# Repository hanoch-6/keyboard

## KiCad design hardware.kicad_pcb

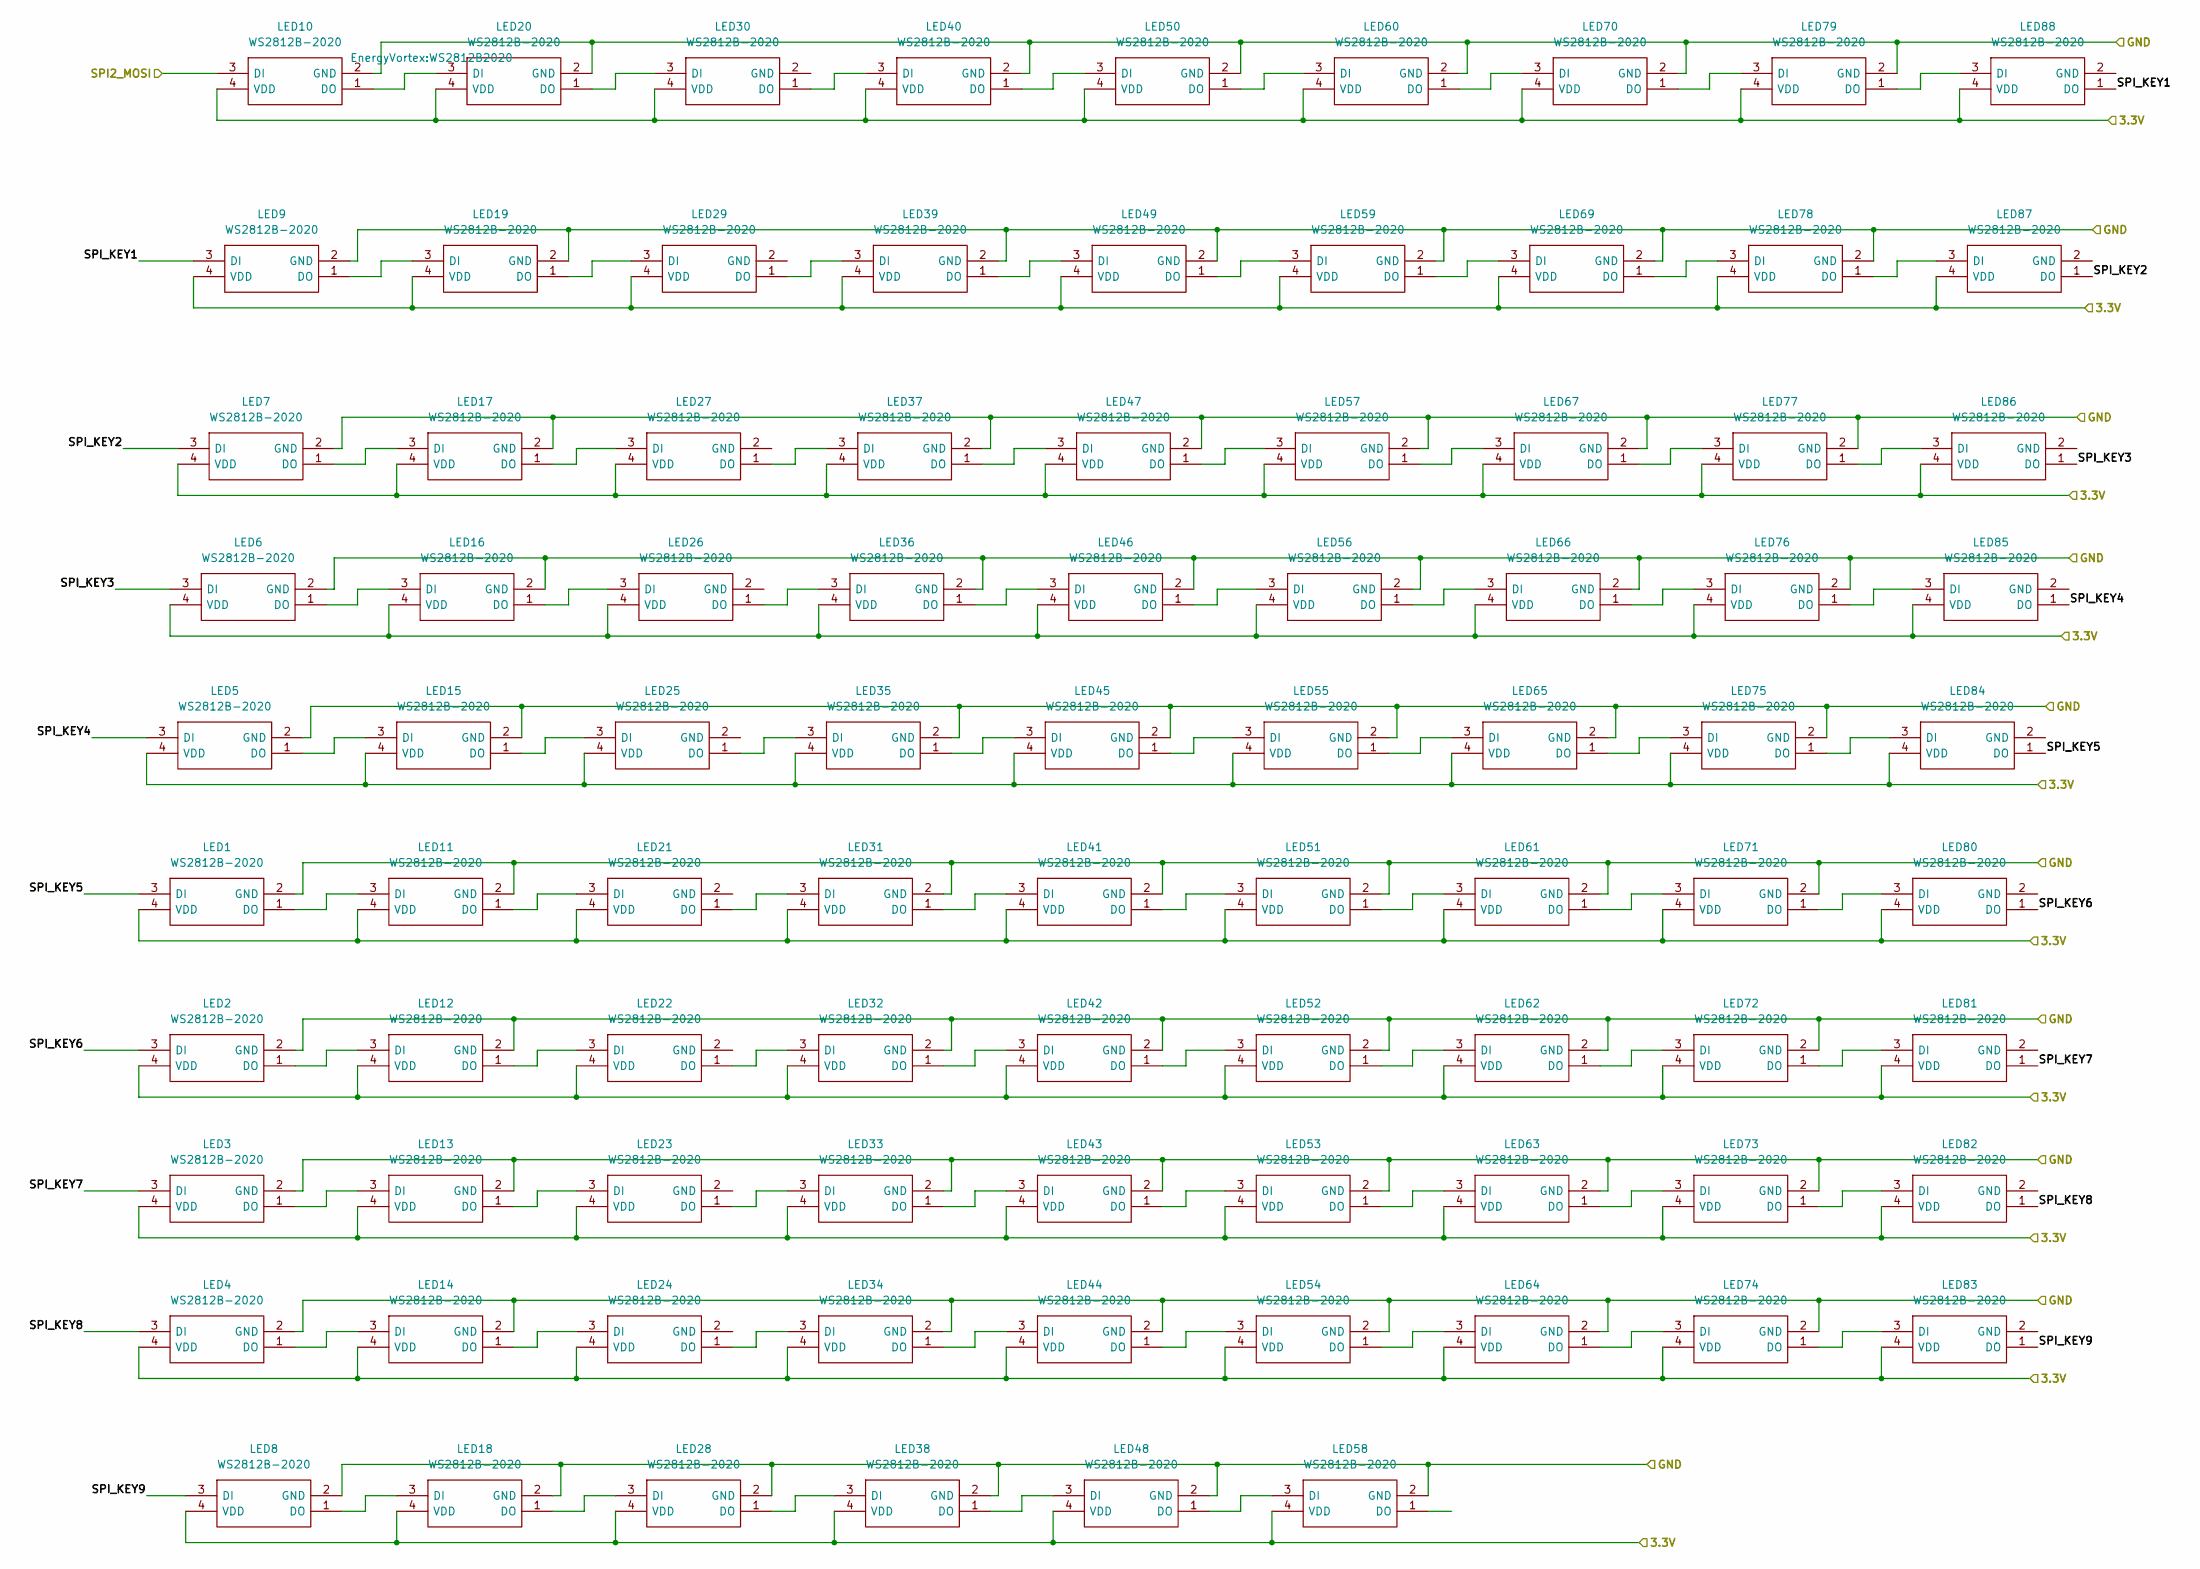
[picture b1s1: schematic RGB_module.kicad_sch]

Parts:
LED1, LED2, LED3, LED4, LED5, LED6, LED7, LED8, LED9, LED10, LED11, LED12, LED13, LED14, LED15, LED16, LED17, LED18, LED19, LED20, LED21, LED22, LED23, LED24, LED25, LED26, LED27, LED28, LED29, LED30, LED31, LED32, LED33, LED34, LED35, LED36, LED37, LED38, LED39, LED40, LED41, LED42, LED43, LED44, LED45, LED46, LED47, LED48, LED49, LED50, LED51, LED52, LED53, LED54, LED55, LED56, LED57, LED58, LED59, LED60, LED61, LED62, LED63, LED64, LED65, LED66, LED67, LED69, LED70, LED71, LED72, LED73, LED74, LED75, LED76, LED77, LED78, LED79, LED80, LED81, LED82, LED83, LED84, LED85, LED86, LED87, LED88: WS2812B-2020; WS2812B2020; Manufacturer_Part_Number WS2812B-2020

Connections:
+3.3V: LED1.4 (VDD), LED2.4 (VDD), LED3.4 (VDD), LED4.4 (VDD), LED5.4 (VDD), LED6.4 (VDD), LED7.4 (VDD), LED8.4 (VDD), LED9.4 (VDD), LED10.4 (VDD), LED11.4 (VDD), LED12.4 (VDD), LED13.4 (VDD), LED14.4 (VDD), LED15.4 (VDD), LED16.4 (VDD), LED17.4 (VDD), LED18.4 (VDD), LED19.4 (VDD), LED20.4 (VDD), LED21.4 (VDD), LED22.4 (VDD), LED23.4 (VDD), LED24.4 (VDD), LED25.4 (VDD), LED26.4 (VDD), LED27.4 (VDD), LED28.4 (VDD), LED29.4 (VDD), LED30.4 (VDD), LED31.4 (VDD), LED32.4 (VDD), LED33.4 (VDD), LED34.4 (VDD), LED35.4 (VDD), LED36.4 (VDD), LED37.4 (VDD), LED38.4 (VDD), LED39.4 (VDD), LED40.4 (VDD), LED41.4 (VDD), LED42.4 (VDD), LED43.4 (VDD), LED44.4 (VDD), LED45.4 (VDD), LED46.4 (VDD), LED47.4 (VDD), LED48.4 (VDD), LED49.4 (VDD), LED50.4 (VDD), LED51.4 (VDD), LED52.4 (VDD), LED53.4 (VDD), LED54.4 (VDD), LED55.4 (VDD), LED56.4 (VDD), LED57.4 (VDD), LED58.4 (VDD), LED59.4 (VDD), LED60.4 (VDD), LED61.4 (VDD), LED62.4 (VDD), LED63.4 (VDD), LED64.4 (VDD), LED65.4 (VDD), LED66.4 (VDD), LED67.4 (VDD), LED69.4 (VDD), LED70.4 (VDD), LED71.4 (VDD), LED72.4 (VDD), LED73.4 (VDD), LED74.4 (VDD), LED75.4 (VDD), LED76.4 (VDD), LED77.4 (VDD), LED78.4 (VDD), LED79.4 (VDD), LED80.4 (VDD), LED81.4 (VDD), LED82.4 (VDD), LED83.4 (VDD), LED84.4 (VDD), LED85.4 (VDD), LED86.4 (VDD), LED87.4 (VDD), LED88.4 (VDD); also elsewhere on the board
/MCU/SPI2_MOSI: LED10.3 (DI); also elsewhere on the board
/RGB_module/SPI_KEY1: LED9.3 (DI), LED88.1 (DO)
/RGB_module/SPI_KEY2: LED7.3 (DI), LED87.1 (DO)
/RGB_module/SPI_KEY3: LED6.3 (DI), LED86.1 (DO)
/RGB_module/SPI_KEY4: LED5.3 (DI), LED85.1 (DO)
/RGB_module/SPI_KEY5: LED1.3 (DI), LED84.1 (DO)
/RGB_module/SPI_KEY6: LED2.3 (DI), LED80.1 (DO)
/RGB_module/SPI_KEY7: LED3.3 (DI), LED81.1 (DO)
/RGB_module/SPI_KEY8: LED4.3 (DI), LED82.1 (DO)
/RGB_module/SPI_KEY9: LED8.3 (DI), LED83.1 (DO)
GND: LED1.2 (GND), LED2.2 (GND), LED3.2 (GND), LED4.2 (GND), LED5.2 (GND), LED6.2 (GND), LED7.2 (GND), LED8.2 (GND), LED9.2 (GND), LED10.2 (GND), LED11.2 (GND), LED12.2 (GND), LED13.2 (GND), LED14.2 (GND), LED15.2 (GND), LED16.2 (GND), LED17.2 (GND), LED18.2 (GND), LED19.2 (GND), LED20.2 (GND), LED28.2 (GND), LED31.2 (GND), LED32.2 (GND), LED33.2 (GND), LED34.2 (GND), LED35.2 (GND), LED36.2 (GND), LED37.2 (GND), LED38.2 (GND), LED39.2 (GND), LED40.2 (GND), LED41.2 (GND), LED42.2 (GND), LED43.2 (GND), LED44.2 (GND), LED45.2 (GND), LED46.2 (GND), LED47.2 (GND), LED48.2 (GND), LED49.2 (GND), LED50.2 (GND), LED51.2 (GND), LED52.2 (GND), LED53.2 (GND), LED54.2 (GND), LED55.2 (GND), LED56.2 (GND), LED57.2 (GND), LED58.2 (GND), LED59.2 (GND), LED60.2 (GND), LED61.2 (GND), LED62.2 (GND), LED63.2 (GND), LED64.2 (GND), LED65.2 (GND), LED66.2 (GND), LED67.2 (GND), LED69.2 (GND), LED70.2 (GND), LED71.2 (GND), LED72.2 (GND), LED73.2 (GND), LED74.2 (GND), LED75.2 (GND), LED76.2 (GND), LED77.2 (GND), LED78.2 (GND), LED79.2 (GND); also elsewhere on the board
unnamed: LED1.1 (DO), LED11.3 (DI)
unnamed: LED10.1 (DO), LED20.3 (DI)
unnamed: LED11.1 (DO), LED21.3 (DI)
unnamed: LED12.1 (DO), LED22.3 (DI)
unnamed: LED2.1 (DO), LED12.3 (DI)
unnamed: LED13.1 (DO), LED23.3 (DI)
unnamed: LED3.1 (DO), LED13.3 (DI)
unnamed: LED14.1 (DO), LED24.3 (DI)
unnamed: LED4.1 (DO), LED14.3 (DI)
unnamed: LED15.1 (DO), LED25.3 (DI)
unnamed: LED5.1 (DO), LED15.3 (DI)
unnamed: LED16.1 (DO), LED26.3 (DI)
unnamed: LED6.1 (DO), LED16.3 (DI)
unnamed: LED17.1 (DO), LED27.3 (DI)
unnamed: LED7.1 (DO), LED17.3 (DI)
unnamed: LED18.1 (DO), LED28.3 (DI)
unnamed: LED8.1 (DO), LED18.3 (DI)
unnamed: LED19.1 (DO), LED29.3 (DI)
unnamed: LED9.1 (DO), LED19.3 (DI)
unnamed: LED20.1 (DO), LED30.3 (DI)
unnamed: LED21.1 (DO), LED31.3 (DI)
unnamed: LED22.1 (DO), LED32.3 (DI)
unnamed: LED23.1 (DO), LED33.3 (DI)
unnamed: LED24.1 (DO), LED34.3 (DI)
unnamed: LED25.1 (DO), LED35.3 (DI)
unnamed: LED26.1 (DO), LED36.3 (DI)
unnamed: LED27.1 (DO), LED37.3 (DI)
unnamed: LED28.1 (DO), LED38.3 (DI)
unnamed: LED29.1 (DO), LED39.3 (DI)
unnamed: LED30.1 (DO), LED40.3 (DI)
unnamed: LED31.1 (DO), LED41.3 (DI)
unnamed: LED32.1 (DO), LED42.3 (DI)
unnamed: LED33.1 (DO), LED43.3 (DI)
unnamed: LED34.1 (DO), LED44.3 (DI)
unnamed: LED35.1 (DO), LED45.3 (DI)
unnamed: LED36.1 (DO), LED46.3 (DI)
unnamed: LED37.1 (DO), LED47.3 (DI)
unnamed: LED38.1 (DO), LED48.3 (DI)
unnamed: LED39.1 (DO), LED49.3 (DI)
unnamed: LED40.1 (DO), LED50.3 (DI)
unnamed: LED41.1 (DO), LED51.3 (DI)
unnamed: LED42.1 (DO), LED52.3 (DI)
unnamed: LED43.1 (DO), LED53.3 (DI)
unnamed: LED44.1 (DO), LED54.3 (DI)
unnamed: LED45.1 (DO), LED55.3 (DI)
unnamed: LED46.1 (DO), LED56.3 (DI)
unnamed: LED47.1 (DO), LED57.3 (DI)
unnamed: LED48.1 (DO), LED58.3 (DI)
unnamed: LED49.1 (DO), LED59.3 (DI)
unnamed: LED50.1 (DO), LED60.3 (DI)
unnamed: LED51.1 (DO), LED61.3 (DI)
unnamed: LED52.1 (DO), LED62.3 (DI)
unnamed: LED53.1 (DO), LED63.3 (DI)
unnamed: LED54.1 (DO), LED64.3 (DI)
unnamed: LED55.1 (DO), LED65.3 (DI)
unnamed: LED56.1 (DO), LED66.3 (DI)
unnamed: LED57.1 (DO), LED67.3 (DI)
unnamed: LED59.1 (DO), LED69.3 (DI)
unnamed: LED60.1 (DO), LED70.3 (DI)
unnamed: LED61.1 (DO), LED71.3 (DI)
unnamed: LED62.1 (DO), LED72.3 (DI)
unnamed: LED63.1 (DO), LED73.3 (DI)
unnamed: LED64.1 (DO), LED74.3 (DI)
unnamed: LED65.1 (DO), LED75.3 (DI)
unnamed: LED66.1 (DO), LED76.3 (DI)
unnamed: LED67.1 (DO), LED77.3 (DI)
unnamed: LED69.1 (DO), LED78.3 (DI)
unnamed: LED70.1 (DO), LED79.3 (DI)
unnamed: LED71.1 (DO), LED80.3 (DI)
unnamed: LED72.1 (DO), LED81.3 (DI)
unnamed: LED73.1 (DO), LED82.3 (DI)
unnamed: LED74.1 (DO), LED83.3 (DI)
unnamed: LED75.1 (DO), LED84.3 (DI)
unnamed: LED76.1 (DO), LED85.3 (DI)
unnamed: LED77.1 (DO), LED86.3 (DI)
unnamed: LED78.1 (DO), LED87.3 (DI)
unnamed: LED79.1 (DO), LED88.3 (DI)

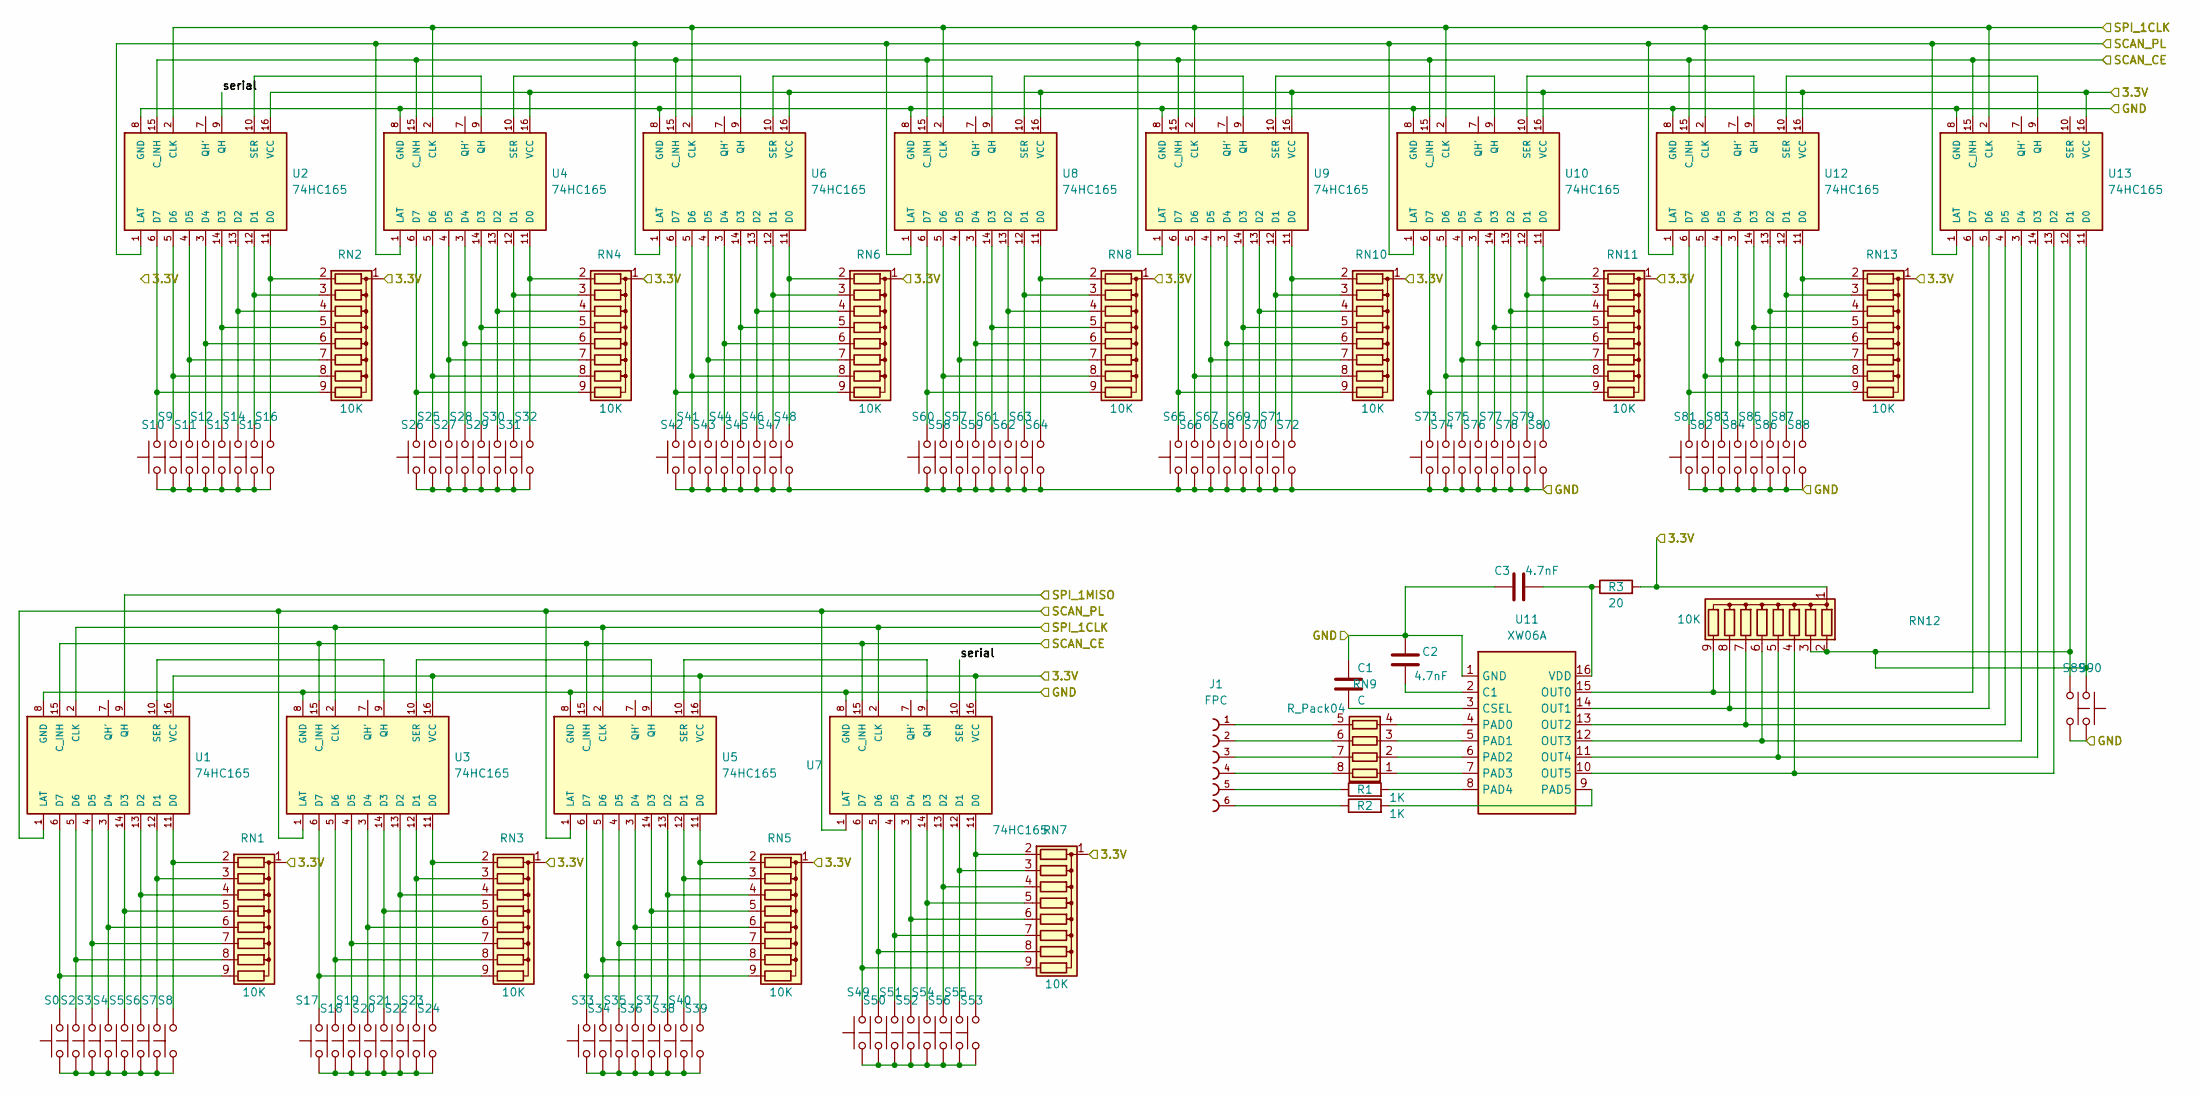
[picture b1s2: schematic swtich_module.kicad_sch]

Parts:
C1: C; C_0603_1608Metric
C2, C3: 4.7nF; C_0603_1608Metric
J1: FPC; FPC-0.5mm-6PIN
R1, R2: 1K; R_0603_1608Metric
R3: 20; R_0603_1608Metric
RN1, RN2, RN3, RN4, RN5, RN6, RN7, RN8, RN10, RN11, RN12, RN13: 10K; R_Array_Convex_8x0602
RN9: R_Pack04; R_Array_Convex_4x0603
S0, S2, S3, S4, S5, S6, S7, S8, S9, S10, S11, S12, S13, S14, S15, S16, S17, S18, S19, S20, S21, S22, S23, S24, S25, S26, S27, S28, S29, S30, S31, S32, S33, S34, S35, S36, S37, S38, S39, S40, S41, S42, S43, S44, S45, S46, S47, S48, S49, S50, S51, S52, S53, S54, S55, S56, S57, S58, S59, S60, S61, S62, S63, S64, S65, S66, S67, S68, S69, S70, S71, S72, S73, S74, S75, S76, S77, S78, S79, S80, S81, S82, S83, S84, S85, S86, S87, S88, S89, S90: SW_Push; CHERRY-MX-LED
U1, U2, U3, U4, U5, U6, U7, U8, U9, U10, U12, U13: 74HC165; SO-16
U11: XW06A; SOIC-16_3.9x9.9mm_P1.27mm

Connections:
+3.3V: R3.2, RN1.1 (common), RN2.1 (common), RN3.1 (common), RN4.1 (common), RN5.1 (common), RN6.1 (common), RN7.1 (common), RN8.1 (common), RN10.1 (common), RN11.1 (common), RN12.1 (common), RN13.1 (common), U1.16 (VCC), U2.16 (VCC), U3.16 (VCC), U4.16 (VCC), U5.16 (VCC), U6.16 (VCC), U7.16 (VCC), U8.16 (VCC), U9.16 (VCC), U10.16 (VCC), U12.16 (VCC), U13.16 (VCC); also elsewhere on the board
/MCU/SCAN_CE: U1.15 (C_INH), U2.15 (C_INH), U3.15 (C_INH), U4.15 (C_INH), U5.15 (C_INH), U6.15 (C_INH), U7.15 (C_INH), U8.15 (C_INH), U9.15 (C_INH), U10.15 (C_INH), U12.15 (C_INH), U13.15 (C_INH); also elsewhere on the board
/MCU/SCAN_PL: U1.1 (LAT), U2.1 (LAT), U3.1 (LAT), U4.1 (LAT), U5.1 (LAT), U6.1 (LAT), U7.1 (LAT), U8.1 (LAT), U9.1 (LAT), U10.1 (LAT), U12.1 (LAT), U13.1 (LAT); also elsewhere on the board
/MCU/SPI1_CLK: U1.2 (CLK), U2.2 (CLK), U3.2 (CLK), U4.2 (CLK), U5.2 (CLK), U6.2 (CLK), U7.2 (CLK), U8.2 (CLK), U9.2 (CLK), U10.2 (CLK), U12.2 (CLK), U13.2 (CLK); also elsewhere on the board
/MCU/SPI1_MISO: U1.9 (QH); also elsewhere on the board
/swtich_module/serial: U2.9 (QH), U7.10 (SER)
GND: C1.2, C2.2, C3.2, S41.1, S42.1, S43.1, S44.1, S45.1, S46.1, S47.1, S48.1, S57.1, S58.1, S59.1, S60.1, S61.1, S62.1, S63.1, S64.1, S65.1, S66.1, S67.1, S68.1, S69.1, S70.1, S71.1, S72.1, S73.1, S74.1, S75.1, S76.1, S77.1, S78.1, S79.1, S80.1, S81.1, S82.1, S83.1, S84.1, S85.1, S86.1, S87.1, S88.1, S89.1, S90.1, U1.8 (GND), U2.8 (GND), U3.8 (GND), U4.8 (GND), U5.8 (GND), U6.8 (GND), U7.8 (GND), U8.8 (GND), U9.8 (GND), U10.8 (GND), U11.1 (GND), U12.8 (GND), U13.8 (GND); also elsewhere on the board
unnamed: C1.1, U11.3 (CSEL)
unnamed: C2.1, U11.2 (C1)
unnamed: C3.1, R3.1, U11.16 (VDD)
unnamed: J1.1, RN9.5 (R4.2)
unnamed: J1.2, RN9.6 (R3.2)
unnamed: J1.3, RN9.7 (R2.2)
unnamed: J1.4, RN9.8 (R1.2)
unnamed: J1.5, R1.1
unnamed: J1.6, R2.1
unnamed: R1.2, U11.8 (PAD4)
unnamed: R2.2, U11.9 (PAD5)
unnamed: RN1.2 (R1), S8.2, U1.11 (D0)
unnamed: RN1.3 (R2), S7.2, U1.12 (D1)
unnamed: RN1.4 (R3), S6.2, U1.13 (D2)
unnamed: RN1.5 (R4), S5.2, U1.14 (D3)
unnamed: RN1.6 (R5), S4.2, U1.3 (D4)
unnamed: RN1.7 (R6), S3.2, U1.4 (D5)
unnamed: RN1.8 (R7), S2.2, U1.5 (D6)
unnamed: RN1.9 (R8), S0.2, U1.6 (D7)
unnamed: RN2.2 (R1), S16.2, U2.11 (D0)
unnamed: RN2.3 (R2), S15.2, U2.12 (D1)
unnamed: RN2.4 (R3), S14.2, U2.13 (D2)
unnamed: RN2.5 (R4), S13.2, U2.14 (D3)
unnamed: RN2.6 (R5), S12.2, U2.3 (D4)
unnamed: RN2.7 (R6), S11.2, U2.4 (D5)
unnamed: RN2.8 (R7), S9.2, U2.5 (D6)
unnamed: RN2.9 (R8), S10.2, U2.6 (D7)
unnamed: RN3.2 (R1), S24.2, U3.11 (D0)
unnamed: RN3.3 (R2), S23.2, U3.12 (D1)
unnamed: RN3.4 (R3), S22.2, U3.13 (D2)
unnamed: RN3.5 (R4), S21.2, U3.14 (D3)
unnamed: RN3.6 (R5), S20.2, U3.3 (D4)
unnamed: RN3.7 (R6), S19.2, U3.4 (D5)
unnamed: RN3.8 (R7), S18.2, U3.5 (D6)
unnamed: RN3.9 (R8), S17.2, U3.6 (D7)
unnamed: RN4.2 (R1), S32.2, U4.11 (D0)
unnamed: RN4.3 (R2), S31.2, U4.12 (D1)
unnamed: RN4.4 (R3), S30.2, U4.13 (D2)
unnamed: RN4.5 (R4), S29.2, U4.14 (D3)
unnamed: RN4.6 (R5), S28.2, U4.3 (D4)
unnamed: RN4.7 (R6), S27.2, U4.4 (D5)
unnamed: RN4.8 (R7), S25.2, U4.5 (D6)
unnamed: RN4.9 (R8), S26.2, U4.6 (D7)
unnamed: RN5.2 (R1), S39.2, U5.11 (D0)
unnamed: RN5.3 (R2), S40.2, U5.12 (D1)
unnamed: RN5.4 (R3), S38.2, U5.13 (D2)
unnamed: RN5.5 (R4), S37.2, U5.14 (D3)
unnamed: RN5.6 (R5), S36.2, U5.3 (D4)
unnamed: RN5.7 (R6), S35.2, U5.4 (D5)
unnamed: RN5.8 (R7), S34.2, U5.5 (D6)
unnamed: RN5.9 (R8), S33.2, U5.6 (D7)
unnamed: RN6.2 (R1), S48.2, U6.11 (D0)
unnamed: RN6.3 (R2), S47.2, U6.12 (D1)
unnamed: RN6.4 (R3), S46.2, U6.13 (D2)
unnamed: RN6.5 (R4), S45.2, U6.14 (D3)
unnamed: RN6.6 (R5), S44.2, U6.3 (D4)
unnamed: RN6.7 (R6), S43.2, U6.4 (D5)
unnamed: RN6.8 (R7), S41.2, U6.5 (D6)
unnamed: RN6.9 (R8), S42.2, U6.6 (D7)
unnamed: RN7.2 (R1), S53.2, U7.11 (D0)
unnamed: RN7.3 (R2), S55.2, U7.12 (D1)
unnamed: RN7.4 (R3), S56.2, U7.13 (D2)
unnamed: RN7.5 (R4), S54.2, U7.14 (D3)
unnamed: RN7.6 (R5), S52.2, U7.3 (D4)
unnamed: RN7.7 (R6), S51.2, U7.4 (D5)
unnamed: RN7.8 (R7), S50.2, U7.5 (D6)
unnamed: RN7.9 (R8), S49.2, U7.6 (D7)
unnamed: RN8.2 (R1), S64.2, U8.11 (D0)
unnamed: RN8.3 (R2), S63.2, U8.12 (D1)
unnamed: RN8.4 (R3), S62.2, U8.13 (D2)
unnamed: RN8.5 (R4), S61.2, U8.14 (D3)
unnamed: RN8.6 (R5), S59.2, U8.3 (D4)
unnamed: RN8.7 (R6), S57.2, U8.4 (D5)
unnamed: RN8.8 (R7), S58.2, U8.5 (D6)
unnamed: RN8.9 (R8), S60.2, U8.6 (D7)
unnamed: RN9.1 (R1.1), U11.7 (PAD3)
unnamed: RN9.2 (R2.1), U11.6 (PAD2)
unnamed: RN9.3 (R3.1), U11.5 (PAD1)
unnamed: RN9.4 (R4.1), U11.4 (PAD0)
unnamed: RN10.2 (R1), S72.2, U9.11 (D0)
unnamed: RN10.3 (R2), S71.2, U9.12 (D1)
unnamed: RN10.4 (R3), S70.2, U9.13 (D2)
unnamed: RN10.5 (R4), S69.2, U9.14 (D3)
unnamed: RN10.6 (R5), S68.2, U9.3 (D4)
unnamed: RN10.7 (R6), S67.2, U9.4 (D5)
unnamed: RN10.8 (R7), S66.2, U9.5 (D6)
unnamed: RN10.9 (R8), S65.2, U9.6 (D7)
unnamed: RN11.2 (R1), S80.2, U10.11 (D0)
unnamed: RN11.3 (R2), S79.2, U10.12 (D1)
unnamed: RN11.4 (R3), S78.2, U10.13 (D2)
unnamed: RN11.5 (R4), S77.2, U10.14 (D3)
unnamed: RN11.6 (R5), S76.2, U10.3 (D4)
unnamed: RN11.7 (R6), S75.2, U10.4 (D5)
unnamed: RN11.8 (R7), S74.2, U10.5 (D6)
unnamed: RN11.9 (R8), S73.2, U10.6 (D7)
unnamed: RN12.2 (R1), RN12.3 (R2), S89.2, S90.2, U13.11 (D0), U13.12 (D1)
unnamed: RN12.4 (R3), U11.10 (OUT5), U13.13 (D2)
unnamed: RN12.5 (R4), U11.11 (OUT4), U13.14 (D3)
unnamed: RN12.6 (R5), U11.12 (OUT3), U13.3 (D4)
unnamed: RN12.7 (R6), U11.13 (OUT2), U13.4 (D5)
unnamed: RN12.8 (R7), U11.14 (OUT1), U13.5 (D6)
unnamed: RN12.9 (R8), U11.15 (OUT0), U13.6 (D7)
unnamed: RN13.2 (R1), S88.2, U12.11 (D0)
unnamed: RN13.3 (R2), S87.2, U12.12 (D1)
unnamed: RN13.4 (R3), S86.2, U12.13 (D2)
unnamed: RN13.5 (R4), S85.2, U12.14 (D3)
unnamed: RN13.6 (R5), S84.2, U12.3 (D4)
unnamed: RN13.7 (R6), S83.2, U12.4 (D5)
unnamed: RN13.8 (R7), S82.2, U12.5 (D6)
unnamed: RN13.9 (R8), S81.2, U12.6 (D7)
unnamed: S0.1, S2.1, S3.1, S4.1, S5.1, S6.1, S7.1, S8.1
unnamed: S9.1, S10.1, S11.1, S12.1, S13.1, S14.1, S15.1, S16.1
unnamed: S17.1, S18.1, S19.1, S20.1, S21.1, S22.1, S23.1, S24.1
unnamed: S25.1, S26.1, S27.1, S28.1, S29.1, S30.1, S31.1, S32.1
unnamed: S33.1, S34.1, S35.1, S36.1, S37.1, S38.1, S39.1, S40.1
unnamed: S49.1, S50.1, S51.1, S52.1, S53.1, S54.1, S55.1, S56.1
unnamed: U1.10 (SER), U3.9 (QH)
unnamed: U2.10 (SER), U4.9 (QH)
unnamed: U3.10 (SER), U5.9 (QH)
unnamed: U4.10 (SER), U6.9 (QH)
unnamed: U5.10 (SER), U7.9 (QH)
unnamed: U6.10 (SER), U8.9 (QH)
unnamed: U8.10 (SER), U9.9 (QH)
unnamed: U9.10 (SER), U10.9 (QH)
unnamed: U10.10 (SER), U12.9 (QH)
unnamed: U12.10 (SER), U13.9 (QH)

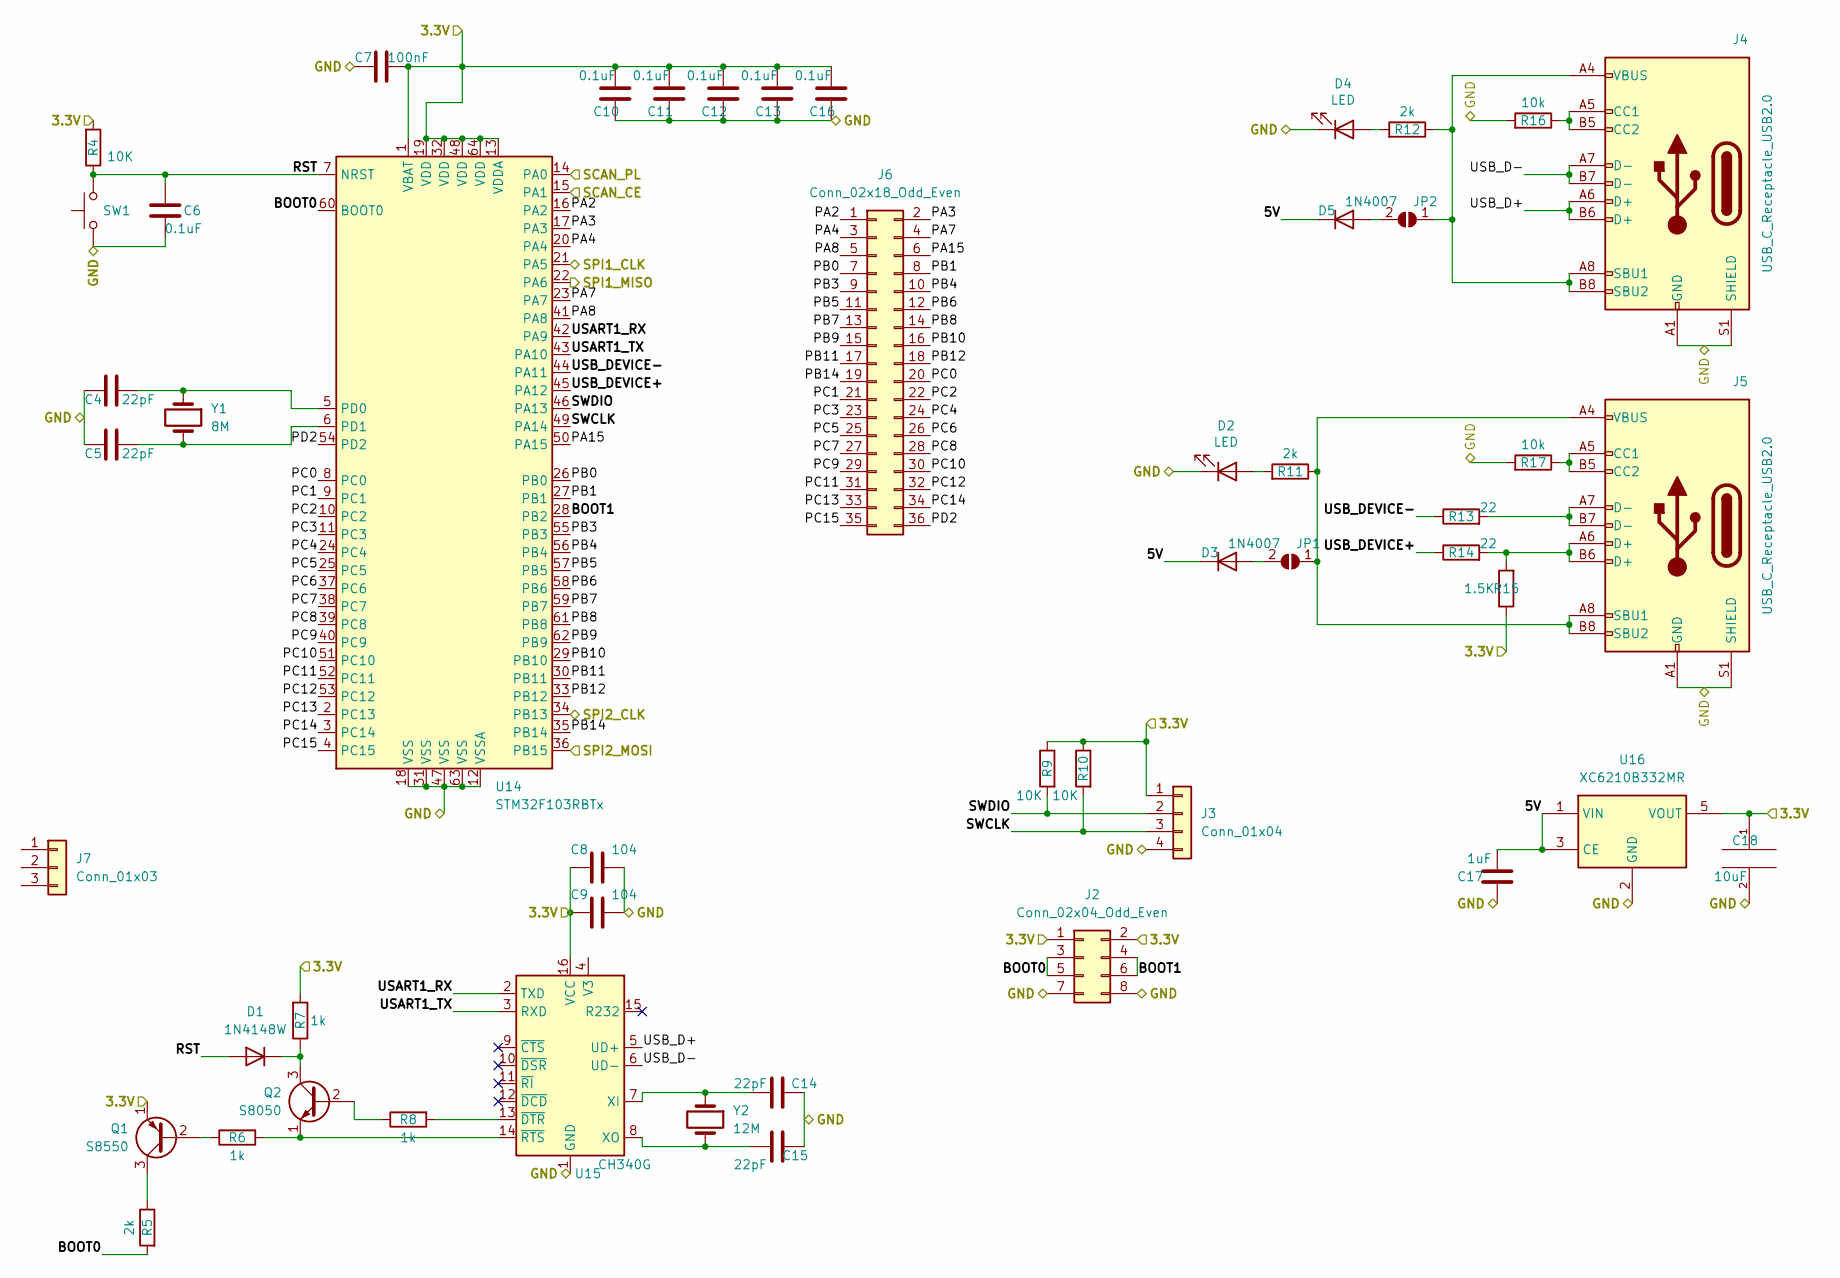
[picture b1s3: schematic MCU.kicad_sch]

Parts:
C4, C5, C14, C15: 22pF; C_0603_1608Metric
C6, C10, C11, C12, C13, C16: 0.1uF; C_0603_1608Metric
C7: 100nF; C_0603_1608Metric
C8, C9: 104; C_0603_1608Metric
C17: 1uF; C_0603_1608Metric
C18: 10uF; C_1206_3216Metric
D1: 1N4148W; D_SOD-123
D2, D4: LED; LED_0805_2012Metric
D3, D5: 1N4007; D_SOD-123F
J2: Conn_02x04_Odd_Even; PinHeader_2x04_P2.54mm_Vertical
J3: Conn_01x04; PinHeader_1x04_P2.54mm_Vertical
J4, J5: USB_C_Receptacle_USB2.0; USB_C_Receptacle_HRO_TYPE-C-31-M-12
J6: Conn_02x18_Odd_Even; PinHeader_2x18_P2.54mm_Vertical
J7: Conn_01x03
JP1, JP2: SolderJumper_2_Open; SolderJumper-2_P1.3mm_Open_TrianglePad1.0x1.5mm
Q1: S8550; SOT-23
Q2: S8050; SOT-23
R4, R9, R10: 10K; R_0603_1608Metric
R5, R11, R12: 2k; R_0603_1608Metric
R6, R7, R8: 1k; R_0603_1608Metric
R13, R14: 22; R_0603_1608Metric
R15: 1.5K; R_0603_1608Metric
R16, R17: 10k; R_0603_1608Metric
SW1: SW_Push; SW_Push_1P1T_NO_6x6mm_H9.5mm
U14: STM32F103RBTx; LQFP-64_10x10mm_P0.5mm
U15: CH340G; SOIC-16_3.9x9.9mm_P1.27mm
U16: XC6210B332MR; SOT-23-5
Y1: 8M; Crystal_SMD_Qantek_QC5CB-2Pin_5x3.2mm
Y2: 12M; Crystal_SMD_Qantek_QC5CB-2Pin_5x3.2mm

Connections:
+3.3V: C7.1, C8.1, C9.1, C10.1, C11.1, C12.1, C13.1, C16.1, C18.1, J2.1, J2.2, J3.1, Q1.1 (E), R4.2, R7.2, R9.1, R10.1, R15.1, U14.1 (VBAT), U14.13 (VDDA), U14.19 (VDD), U14.32 (VDD), U14.48 (VDD), U14.64 (VDD), U15.16 (VCC), U16.5 (VOUT); also elsewhere on the board
/MCU/5V: C17.2, D3.1 (K), D5.1 (K), U16.1 (VIN), U16.3 (CE)
/MCU/BOOT0: J2.3, J2.5, R5.2, U14.60 (BOOT0)
/MCU/BOOT1: J2.4, J2.6, U14.28 (PB2)
/MCU/PA2: J6.1, U14.16 (PA2)
/MCU/PA3: J6.2, U14.17 (PA3)
/MCU/PA4: J6.3, U14.20 (PA4)
/MCU/PA7: J6.4, U14.23 (PA7)
/MCU/PA8: J6.5, U14.41 (PA8)
/MCU/PA15: J6.6, U14.50 (PA15)
/MCU/PB0: J6.7, U14.26 (PB0)
/MCU/PB1: J6.8, U14.27 (PB1)
/MCU/PB3: J6.9, U14.55 (PB3)
/MCU/PB4: J6.10, U14.56 (PB4)
/MCU/PB5: J6.11, U14.57 (PB5)
/MCU/PB6: J6.12, U14.58 (PB6)
/MCU/PB7: J6.13, U14.59 (PB7)
/MCU/PB8: J6.14, U14.61 (PB8)
/MCU/PB9: J6.15, U14.62 (PB9)
/MCU/PB10: J6.16, U14.29 (PB10)
/MCU/PB11: J6.17, U14.30 (PB11)
/MCU/PB12: J6.18, U14.33 (PB12)
/MCU/PB14: J6.19, U14.35 (PB14)
/MCU/PC0: J6.20, U14.8 (PC0)
/MCU/PC1: J6.21, U14.9 (PC1)
/MCU/PC2: J6.22, U14.10 (PC2)
/MCU/PC3: J6.23, U14.11 (PC3)
/MCU/PC4: J6.24, U14.24 (PC4)
/MCU/PC5: J6.25, U14.25 (PC5)
/MCU/PC6: J6.26, U14.37 (PC6)
/MCU/PC7: J6.27, U14.38 (PC7)
/MCU/PC8: J6.28, U14.39 (PC8)
/MCU/PC9: J6.29, U14.40 (PC9)
/MCU/PC10: J6.30, U14.51 (PC10)
/MCU/PC11: J6.31, U14.52 (PC11)
/MCU/PC12: J6.32, U14.53 (PC12)
/MCU/PC13: J6.33, U14.2 (PC13)
/MCU/PC14: J6.34, U14.3 (PC14)
/MCU/PC15: J6.35, U14.4 (PC15)
/MCU/PD2: J6.36, U14.54 (PD2)
/MCU/RST: C6.1, D1.2 (A), R4.1, SW1.2, U14.7 (NRST)
/MCU/SCAN_CE: U14.15 (PA1); also elsewhere on the board
/MCU/SCAN_PL: U14.14 (PA0); also elsewhere on the board
/MCU/SPI1_CLK: U14.21 (PA5); also elsewhere on the board
/MCU/SPI1_MISO: U14.22 (PA6); also elsewhere on the board
/MCU/SPI2_CLK: U14.34 (PB13)
/MCU/SPI2_MOSI: U14.36 (PB15); also elsewhere on the board
/MCU/SWCLK: J3.3, R10.2, U14.49 (PA14)
/MCU/SWDIO: J3.2, R9.2, U14.46 (PA13)
/MCU/USART1_RX: U14.42 (PA9), U15.2 (TXD)
/MCU/USART1_TX: U14.43 (PA10), U15.3 (RXD)
/MCU/USB_D+: J4.A6 (D+), J4.B6 (D+), U15.5 (UD+)
/MCU/USB_D-: J4.A7 (D-), J4.B7 (D-), U15.6 (UD-)
/MCU/USB_DEVICE+: R14.1, U14.45 (PA12)
/MCU/USB_DEVICE-: R13.1, U14.44 (PA11)
GND: C4.2, C5.2, C6.2, C7.2, C8.2, C9.2, C10.2, C11.2, C12.2, C13.2, C14.1, C15.1, C16.2, C17.1, C18.2, D2.1 (K), D4.1 (K), J2.7, J2.8, J3.4, J4.A1 (GND), J4.A12 (GND), J4.B1 (GND), J4.B12 (GND), J4.S1 (SHIELD), J5.A1 (GND), J5.A12 (GND), J5.B1 (GND), J5.B12 (GND), J5.S1 (SHIELD), R16.2, R17.2, SW1.1, U14.12 (VSSA), U14.18 (VSS), U14.31 (VSS), U14.47 (VSS), U14.63 (VSS), U15.1 (GND), U16.2 (GND); also elsewhere on the board
unnamed: C4.1, U14.5 (PD0), Y1.1
unnamed: C5.1, U14.6 (PD1), Y1.2
unnamed: C14.2, U15.7 (XI), Y2.1
unnamed: C15.2, U15.8 (XO), Y2.2
unnamed: D1.1 (K), Q2.3 (C), R7.1
unnamed: D2.2 (A), R11.2
unnamed: D3.2 (A), JP1.2 (B)
unnamed: D4.2 (A), R12.2
unnamed: D5.2 (A), JP2.2 (B)
unnamed: J4.A4 (VBUS), J4.A8 (SBU1), J4.A9 (VBUS), J4.B4 (VBUS), J4.B8 (SBU2), J4.B9 (VBUS), JP2.1 (A), R12.1
unnamed: J4.A5 (CC1), J4.B5 (CC2), R16.1
unnamed: J5.A4 (VBUS), J5.A8 (SBU1), J5.A9 (VBUS), J5.B4 (VBUS), J5.B8 (SBU2), J5.B9 (VBUS), JP1.1 (A), R11.1
unnamed: J5.A5 (CC1), J5.B5 (CC2), R17.1
unnamed: J5.A6 (D+), J5.B6 (D+), R14.2, R15.2
unnamed: J5.A7 (D-), J5.B7 (D-), R13.2
unnamed: Q1.2 (B), R6.1
unnamed: Q1.3 (C), R5.1
unnamed: Q2.1 (E), R6.2, U15.14 (~RTS)
unnamed: Q2.2 (B), R8.1
unnamed: R8.2, U15.13 (~DTR)

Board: 2 copper layers, 350 parts (6 on the bottom side), 288 nets, no tracks yet.

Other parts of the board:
S1, S1#2, S1#3, S1#4, S1#5, S1#6, S1#7, S1#8, S1#9, S1#10, S1#11, S1#12, S1#13, S1#14, S1#15, S1#16, S1#17, S1#18, S1#19, S1#20, S1#21, S1#22, S1#23, S1#24, S1#25, S1#26, S1#27, S1#28, S1#29, S1#30, S1#31, S1#32, S1#33, S1#34, S1#35, S1#36, S1#37, S1#38, S1#39, S1#40, S1#41, S1#42, S1#43, S1#44, S1#45, S1#46, S1#47, S1#48, S1#49, S1#50, S1#51, S1#52, S1#53, S1#54, S1#55, S1#56, S1#57, S1#58, S1#59, S1#60, S1#61, S1#62, S1#63, S1#64, S1#65, S1#66, S1#67, S1#68, S1#69, S1#70, S1#71, S1#72, S1#73, S1#74, S1#75, S1#76, S1#77, S1#78, S1#79, S1#80, S1#81, S1#82, S1#83, S1#84, S1#85, S1#86, S1#87, S1#88, S1#89, S1#90, S1#91: SW_Push; SW_Cherry_MX_1.00u_PCB

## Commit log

2023-03-28 first merge
